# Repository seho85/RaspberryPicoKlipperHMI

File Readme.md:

>  **DISCLAIMER:**
>   This project project is made by an hobbyist.
>   Everything described here is without guarantee, so if you perform something described here, **YOU DO IT ON YOUR OWN RISK**
>
ASCII Display for Klipper
=========================

This project contains the ASCII Display that I use with Klipper.

It's controlled by a Rotary Encoder and few Buttons and controllable LEDs.

Features:
* Raspberry Pi Pico for easy klipper integration
* 20x4 LCD
  * Controlled by rotary encoder with push button
  * Background LED brightness controllable from klipper
* 8 Pushbuttons for custom actions in klipper
* 7 LEDs triggerable from klipper.
* Single MicroUSB cable for connection to klipper host machine.

See [General](doc/General.md) for details.

KiCAD Projects
--------------
Two KiCAD projects can be found.

* _RPiPicoKlipperAsciiHMI_
  * Schematics I used on my breadboard during "proof of concept" phase.
* _RPiPicoAsciiHMI2_
  * [Schematics](https://github.com/seho85/RaspberryPicoKlipperHMI/raw/master/RPiPicoAsciiHMI2/Schematic.pdf)) for the HMI that I use with klipper.

See [KiCAD Projects](doc/KiCAD_Projects.md)

PCBs
----
Basically the whole HMI consists of two PCBs.

* The [Button PCB](doc/BTN_LED_PCB.md)
    * Buttons (with integrated LEDs)
* The [Main PCB](doc/Main_PCB.md)
  * all other components.

FreeCAD Projects
----------------
In the _FreeCAD_ folder two FreeCAD Projects for the case and the backcover can be found.

Hardware used
-------------
The major components used for the HMI can be found here [Hardware Listing](doc/Hardware.md)

For a complete listing of all the components please refer to the KiCAD Project.

MicroPython
-----------
During the creation process of the HMI I created a few MicroPython scripts to test a components.

See [MicroPython Testing Script](doc/MicroPython.md)

Klipper Configuration
---------------------
See [Klipper Config](doc/klipper_config.md)

How to Flash Raspberry Pi Pico
------------------------------
See [Flashing](doc/Flashing.md)

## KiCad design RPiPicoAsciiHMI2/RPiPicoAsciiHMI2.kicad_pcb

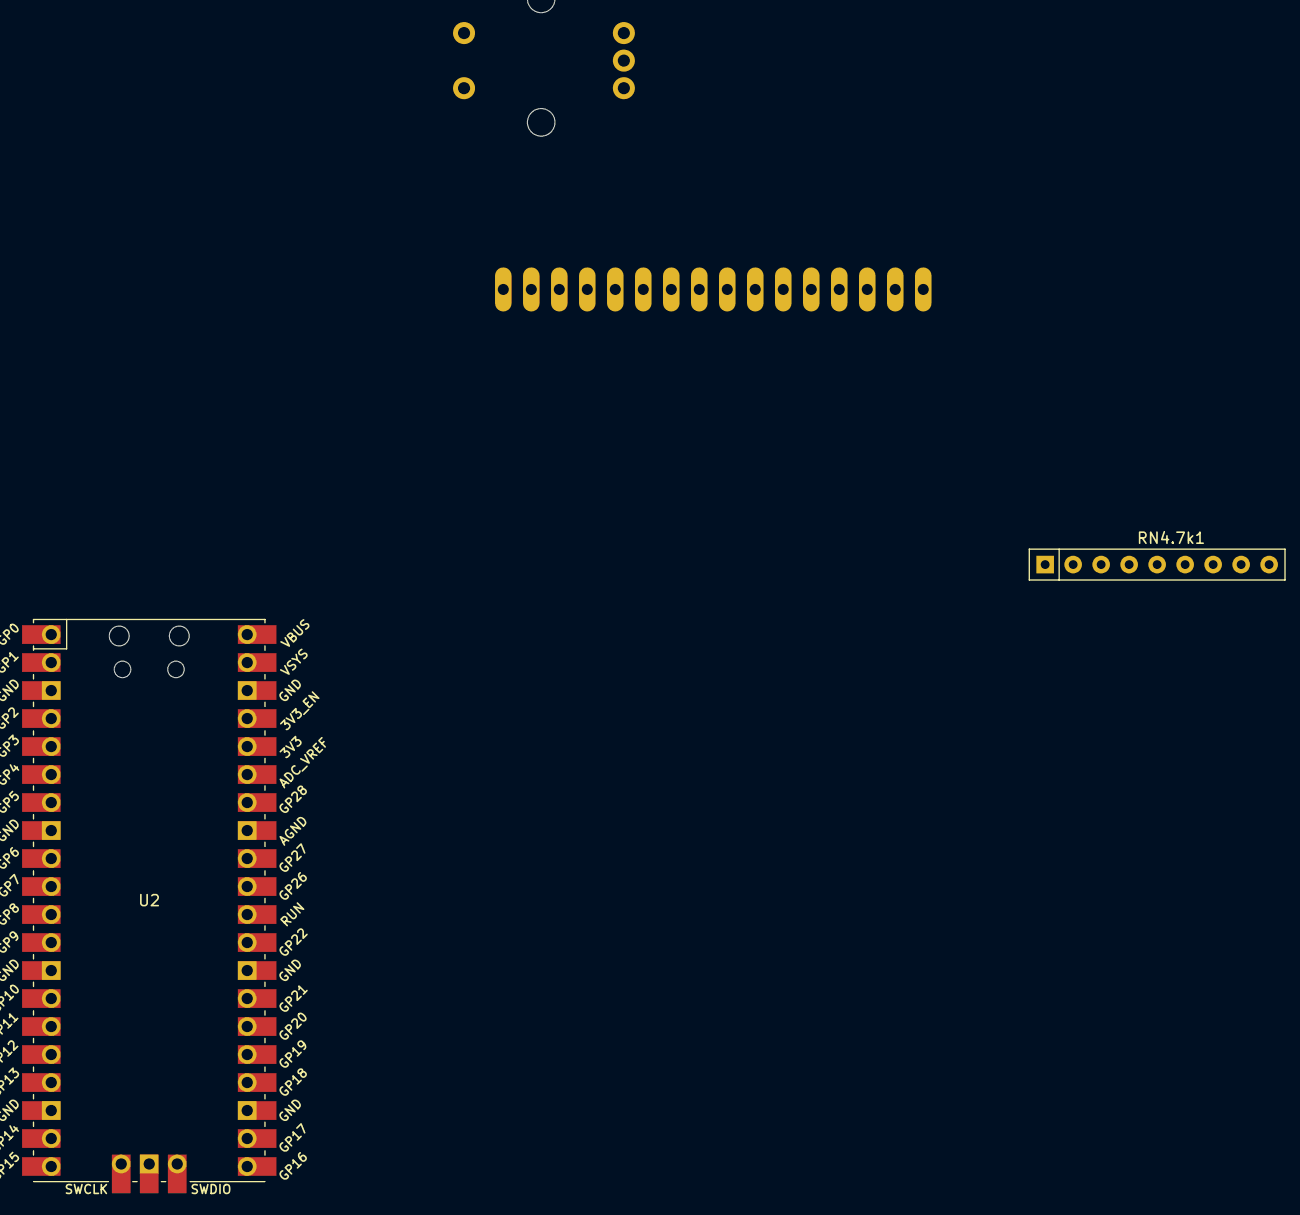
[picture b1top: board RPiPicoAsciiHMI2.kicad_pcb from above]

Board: 2 copper layers, 4 parts (0 on the bottom side), 2 nets, no tracks yet.

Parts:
RN4.7k1: R_Network08; R_Array_SIP9
U1: LCD-20X4; LCD-20x4
U2: Pico; RPi_Pico_SMD_TH
U3: ROTARY_ENCODER_MODULE; ROTARY_ENCODER

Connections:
+5V: U1.2 (VDD), U2.40 (VBUS)
GND: U1.1 (VSS), U1.5 (R/W), U2.28 (GND)

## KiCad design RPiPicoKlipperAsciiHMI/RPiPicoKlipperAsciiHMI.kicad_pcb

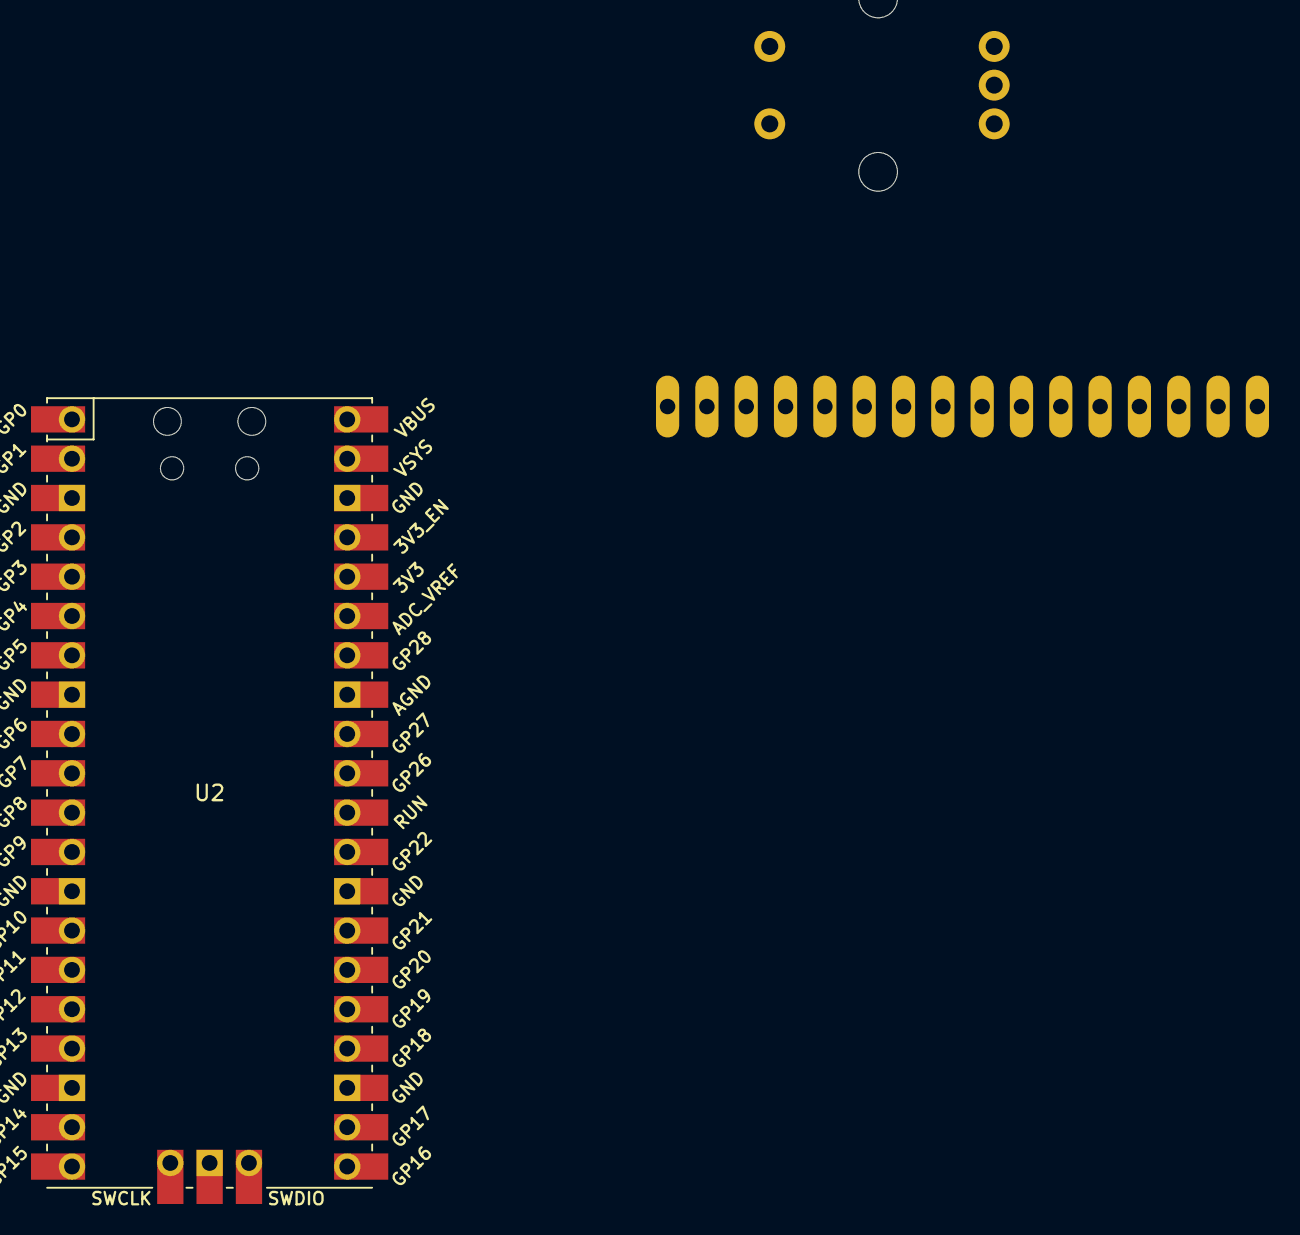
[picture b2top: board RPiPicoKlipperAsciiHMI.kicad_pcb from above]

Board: 2 copper layers, 3 parts (0 on the bottom side), 8 nets, no tracks yet.

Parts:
U1: LCD-20X4; LCD-20x4
U2: Pico; RPi_Pico_SMD_TH
U3: ROTARY_ENCODER_MODULE; ROTARY_ENCODER

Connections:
+5V: U1.2 (VDD), U2.40 (VBUS)
/LCD_D4: U1.11 (DB4), U2.7 (GPIO5)
/LCD_D5: U1.12 (DB5), U2.6 (GPIO4)
/LCD_D6: U1.13 (DB6), U2.5 (GPIO3)
/LCD_D7: U1.14 (DB7), U2.4 (GPIO2)
/LCD_E: U1.6 (E), U2.2 (GPIO1)
/LCD_RS: U1.4 (RS), U2.1 (GPIO0)
GND: U1.1 (VSS), U1.5 (R/W), U2.39 (VSYS)

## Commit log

2022-03-03 Initial commit.
    Revision 1 of the KiCAD project and some documentation.
2022-03-03 added link to schematic
2022-03-03 Added disclaimer
2022-04-09 Begun documentation
    Created pages for General, MainPCB and ButtonPCB
    Also added a few pictures of the PCBs.
2022-04-10 Added FreeCAD Projects for Case and Cover
    Added case for the HMI and the cover.
2022-04-10 Added KiCAD Project of HMI
    Added the KiCAD project for the HMI that is actually used by me.
2022-04-10 Added latest Version of POC KiCAD Project
2022-04-10 Added gitignore to ignore older versions of the FreeCAD Projects
2022-04-10 Updated documentation and add picture of HMI in usage.
2022-04-10 Removed old schematics.pdf
2022-04-10 Updated documentation.
    Moved a few older md files to doc folder and extended the documentation.
2022-04-10 Revert "Updated documentation."
    This reverts commit dc4e633a0653703a90d16450be3b38737c40c757.
2022-04-10 Restored older Readme.md
2022-04-10 Fixed links in readme
2022-04-10 Updated documentation
2022-04-10 Updated Readme.md
    fixed link to schematics.pdf file.
